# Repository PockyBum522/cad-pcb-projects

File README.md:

# cad-pcb-projects
Various PCB projects, mostly in KiCAD

## WT32-ETH01 Programming Shield

## ESP32-DevKitC-1 Prototype Shield

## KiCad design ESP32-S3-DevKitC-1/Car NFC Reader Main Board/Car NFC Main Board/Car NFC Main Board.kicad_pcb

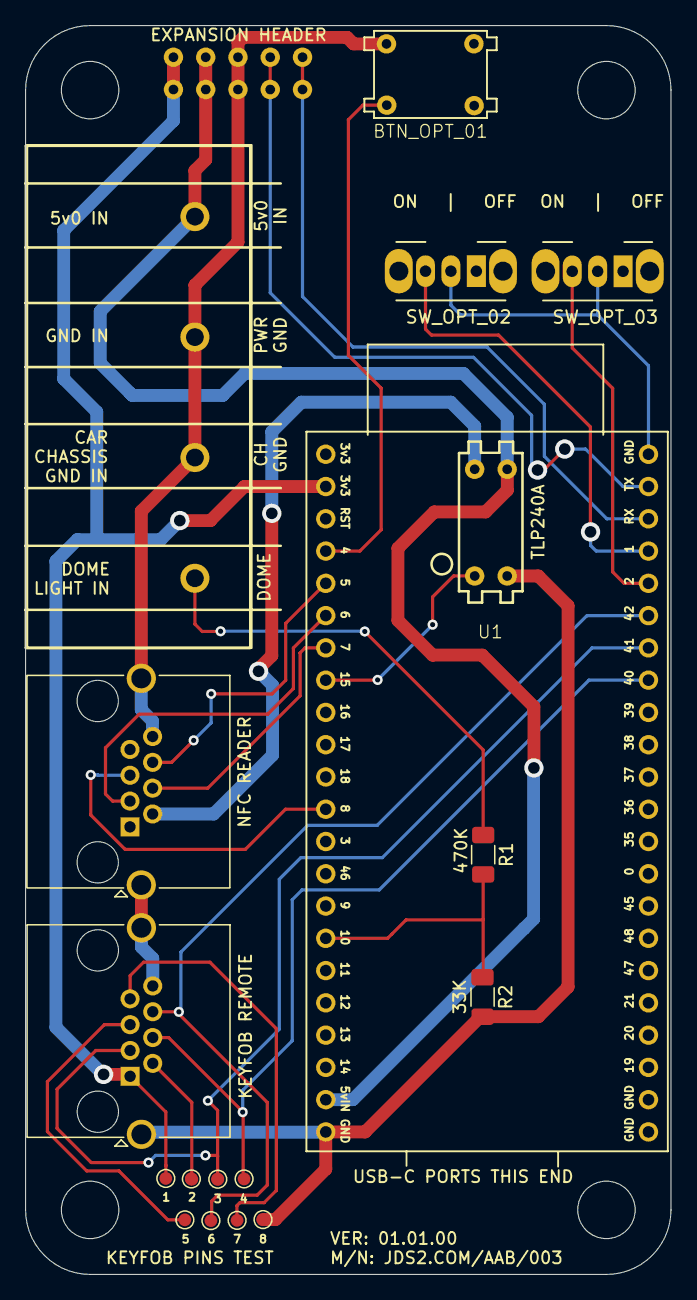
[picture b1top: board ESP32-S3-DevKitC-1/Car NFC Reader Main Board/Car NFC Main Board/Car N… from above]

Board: 2 copper layers, 50.8 x 98.3 mm, 11 parts (0 on the bottom side), 19 nets.

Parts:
BTN_OPT_01: SW_Push_Momentary; MOMENTARY_BUTTON
J1: YK441 Screw Terminal Block_CAR_NFC
J2, J3: AMPHENOL_RJHSE-5380-ND; RJ45_Amphenol_RJHSE5380
J4: 10_PIN_HEADER; 8_PIN_HEADER
R1, R2: R; R_1206_3216Metric_Pad1.30x1.75mm_HandSolder
SW_OPT_02, SW_OPT_03: SW_SPDT; SW_CuK_OS102011MA1QN1_SPDT_Angled
U1: TLP240A
U2: ESP32-S3-DevKitC-1_DAVID; ESP32-S3-DEVKITC_DAVID

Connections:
+3.3V: J2.1 (1/WHT-ORANGE), J4.3 (3V3), U2.52 (3V3)
+5V: J1.1, J4.2 (5V), U1.4 (C), U2.51 (5v0_IN)
/DOME: J1.4, R1.1
GND: BTN_OPT_01.1, J1.2, J1.3, J2.8 (8/BROWN), J2.SH (SHIELD), J3.7 (7/WHT-BROWN), J3.SH (SHIELD), J4.1 (GND), R2.2, SW_OPT_02.2 (B), SW_OPT_03.2 (B), U1.6 (K), U2.50 (GND)
unnamed: J2.3 (3/WHT-GREEN), U2.41 (GPIO41_MTMS/CLK_OUT1)
unnamed: J2.4 (4/BLUE), U2.40 (GPIO40_MTDO/CLK_OUT2)
unnamed: J2.6 (6/GREEN), U2.42 (GPIO42_MTMS)
unnamed: J3.2 (2/ORANGE), U1.3 (E)
unnamed: J3.3 (3/WHT-GREEN), U2.6 (GPIO6_TOUCH6/ADC1_CH5/RTC)
unnamed: J3.4 (4/BLUE), U2.7 (GPIO7_TOUCH7/ADC1_CH6/RTC)
unnamed: J3.5 (5/WHT-BLUE), U2.8 (GPIO8_TOUCH8/ADC1_CH7/RTC)
unnamed: J3.6 (6/GREEN), U2.5 (GPIO5_TOUCH5/ADC1_CH4/RTC)
unnamed: J4.5 (RX0), U2.44 (GPIO44_U0RXD/CLK_OUT2)
unnamed: J4.4 (TX0), U2.43 (GPIO43_U0TXD/CLK_OUT1)
unnamed: SW_OPT_02.3 (C), U2.1 (GPIO1_TOUCH1/ADC1_CH0/RTC)
unnamed: SW_OPT_03.3 (C), U2.2 (GPIO2_TOUCH2/ADC1_CH1/RTC)
unnamed: U1.1 (A), U2.15 (GPIO15_U0RTS/ADC2_CH4/XTAL_32K_P/RTC)
unnamed: BTN_OPT_01.2, U2.4 (GPIO4_TOUCH4/ADC1_CH3/RTC)
unnamed: R1.2, R2.1, U2.10 (GPIO10_TOUCH10/ADC1_CH9/FSPICS0/SUBSPIC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)

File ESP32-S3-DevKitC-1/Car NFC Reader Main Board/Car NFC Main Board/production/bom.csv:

Designator,Footprint,Quantity,Value,LCSC Part #
BTN_OPT_01,MOMENTARY_BUTTON,1,SW_Push_Momentary,
J1,YK441 Screw Terminal Block_CAR_NFC,1,~,
"J2, J3",RJ45_Amphenol_RJHSE5380,2,AMPHENOL_RJHSE-5380-ND,
J4,8_PIN_HEADER,1,10_PIN_HEADER,
"R1, R2",1206,2,R,
"SW_OPT_02, SW_OPT_03",SW_CuK_OS102011MA1QN1_SPDT_Angled,2,SW_SPDT,
U1,TLP240A,1,TLP240A,
U2,ESP32-S3-DEVKITC_DAVID,1,ESP32-S3-DevKitC-1_DAVID,

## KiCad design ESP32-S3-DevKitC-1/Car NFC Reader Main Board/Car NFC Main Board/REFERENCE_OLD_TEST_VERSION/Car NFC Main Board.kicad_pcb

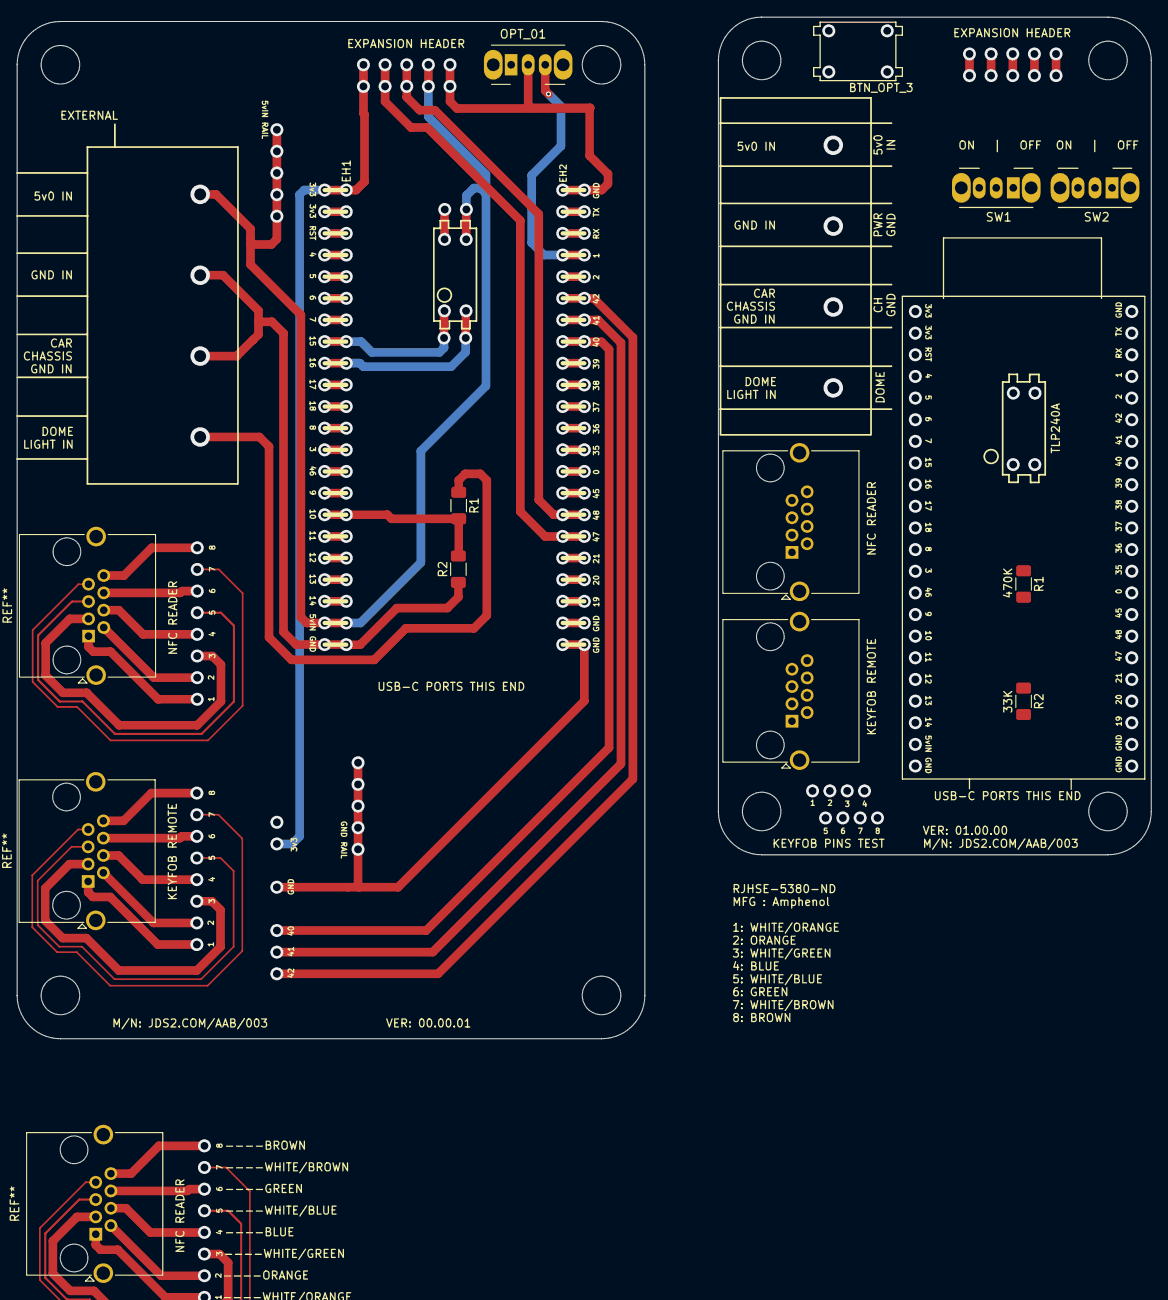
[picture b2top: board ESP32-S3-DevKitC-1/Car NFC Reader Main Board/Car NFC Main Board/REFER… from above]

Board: 2 copper layers, 133.1 x 119.9 mm, 7 parts (0 on the bottom side), 3 nets.

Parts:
OPT_01: SW_Slide_SPDT_Angled_CK_OS102011MA1Q
R1, R1#2: 470K; R_1206_3216Metric_Pad1.30x1.75mm_HandSolder
R2: 33K; R_1206_3216Metric_Pad1.30x1.75mm_HandSolder
R2#2: 200R; R_1206_3216Metric_Pad1.30x1.75mm_HandSolder
SW1, SW2: SW_SPDT; SW_CuK_OS102011MA1QN1_SPDT_Angled

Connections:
GND: OPT_01.2, R2.2, R2#2.1, SW1.2 (B), SW2.2 (B)
unnamed: R1.2, R2.1
POST_DIVIDER_DOME: R1#2.2, R2#2.2

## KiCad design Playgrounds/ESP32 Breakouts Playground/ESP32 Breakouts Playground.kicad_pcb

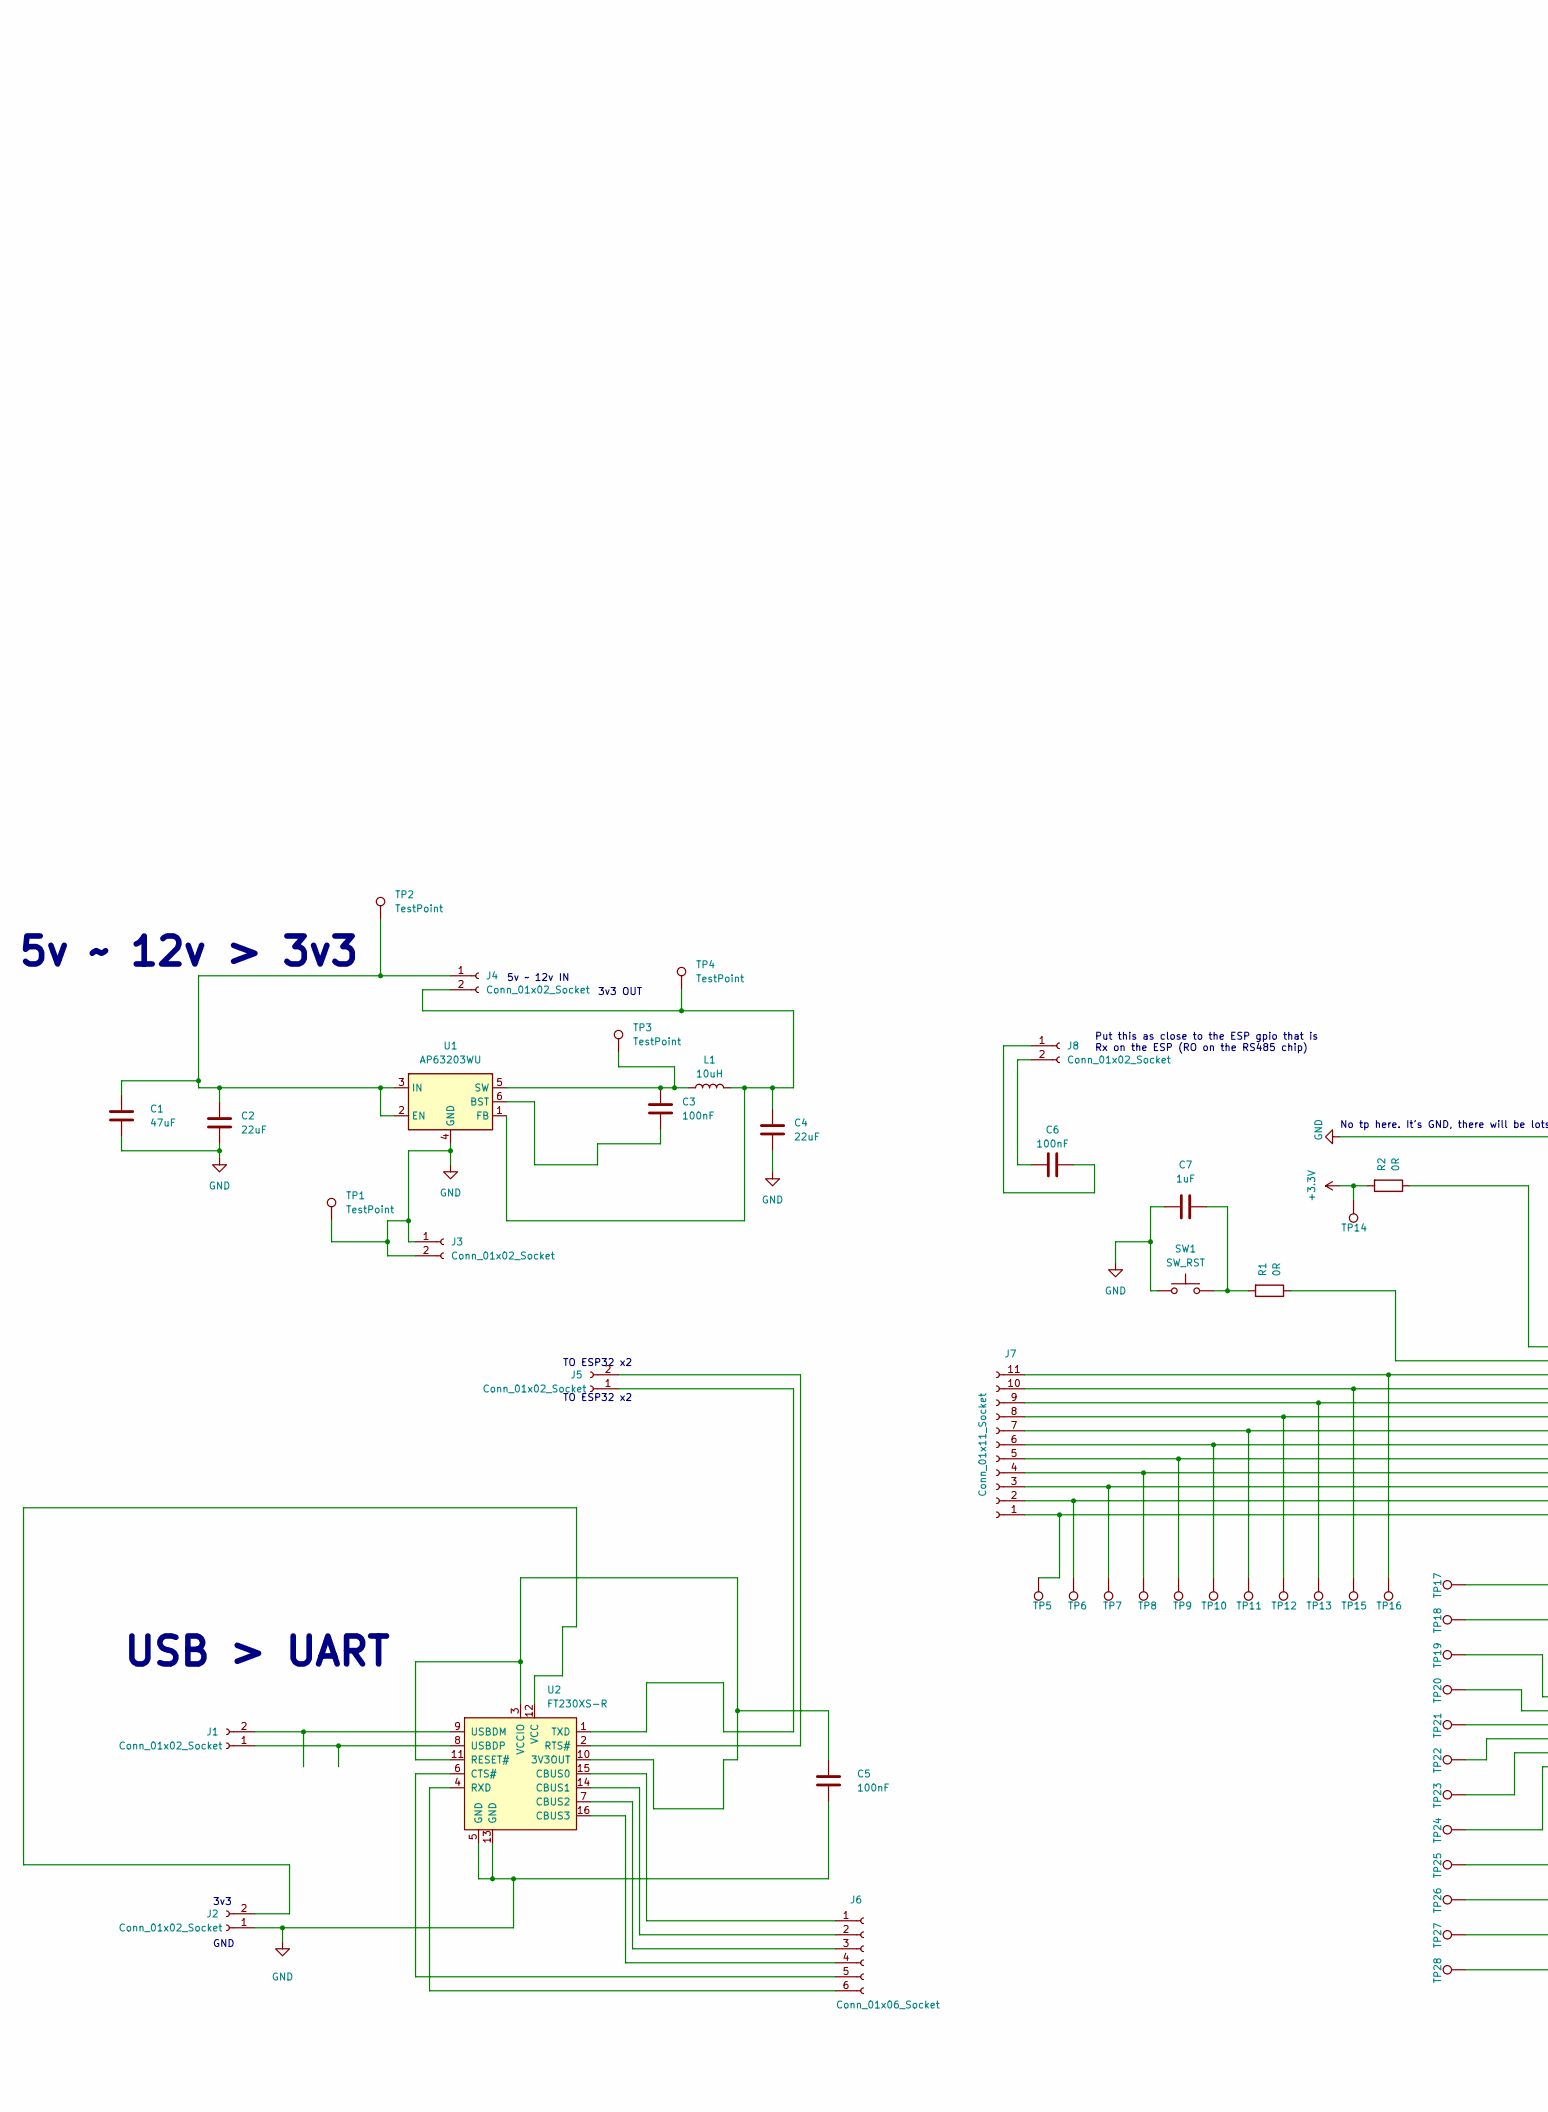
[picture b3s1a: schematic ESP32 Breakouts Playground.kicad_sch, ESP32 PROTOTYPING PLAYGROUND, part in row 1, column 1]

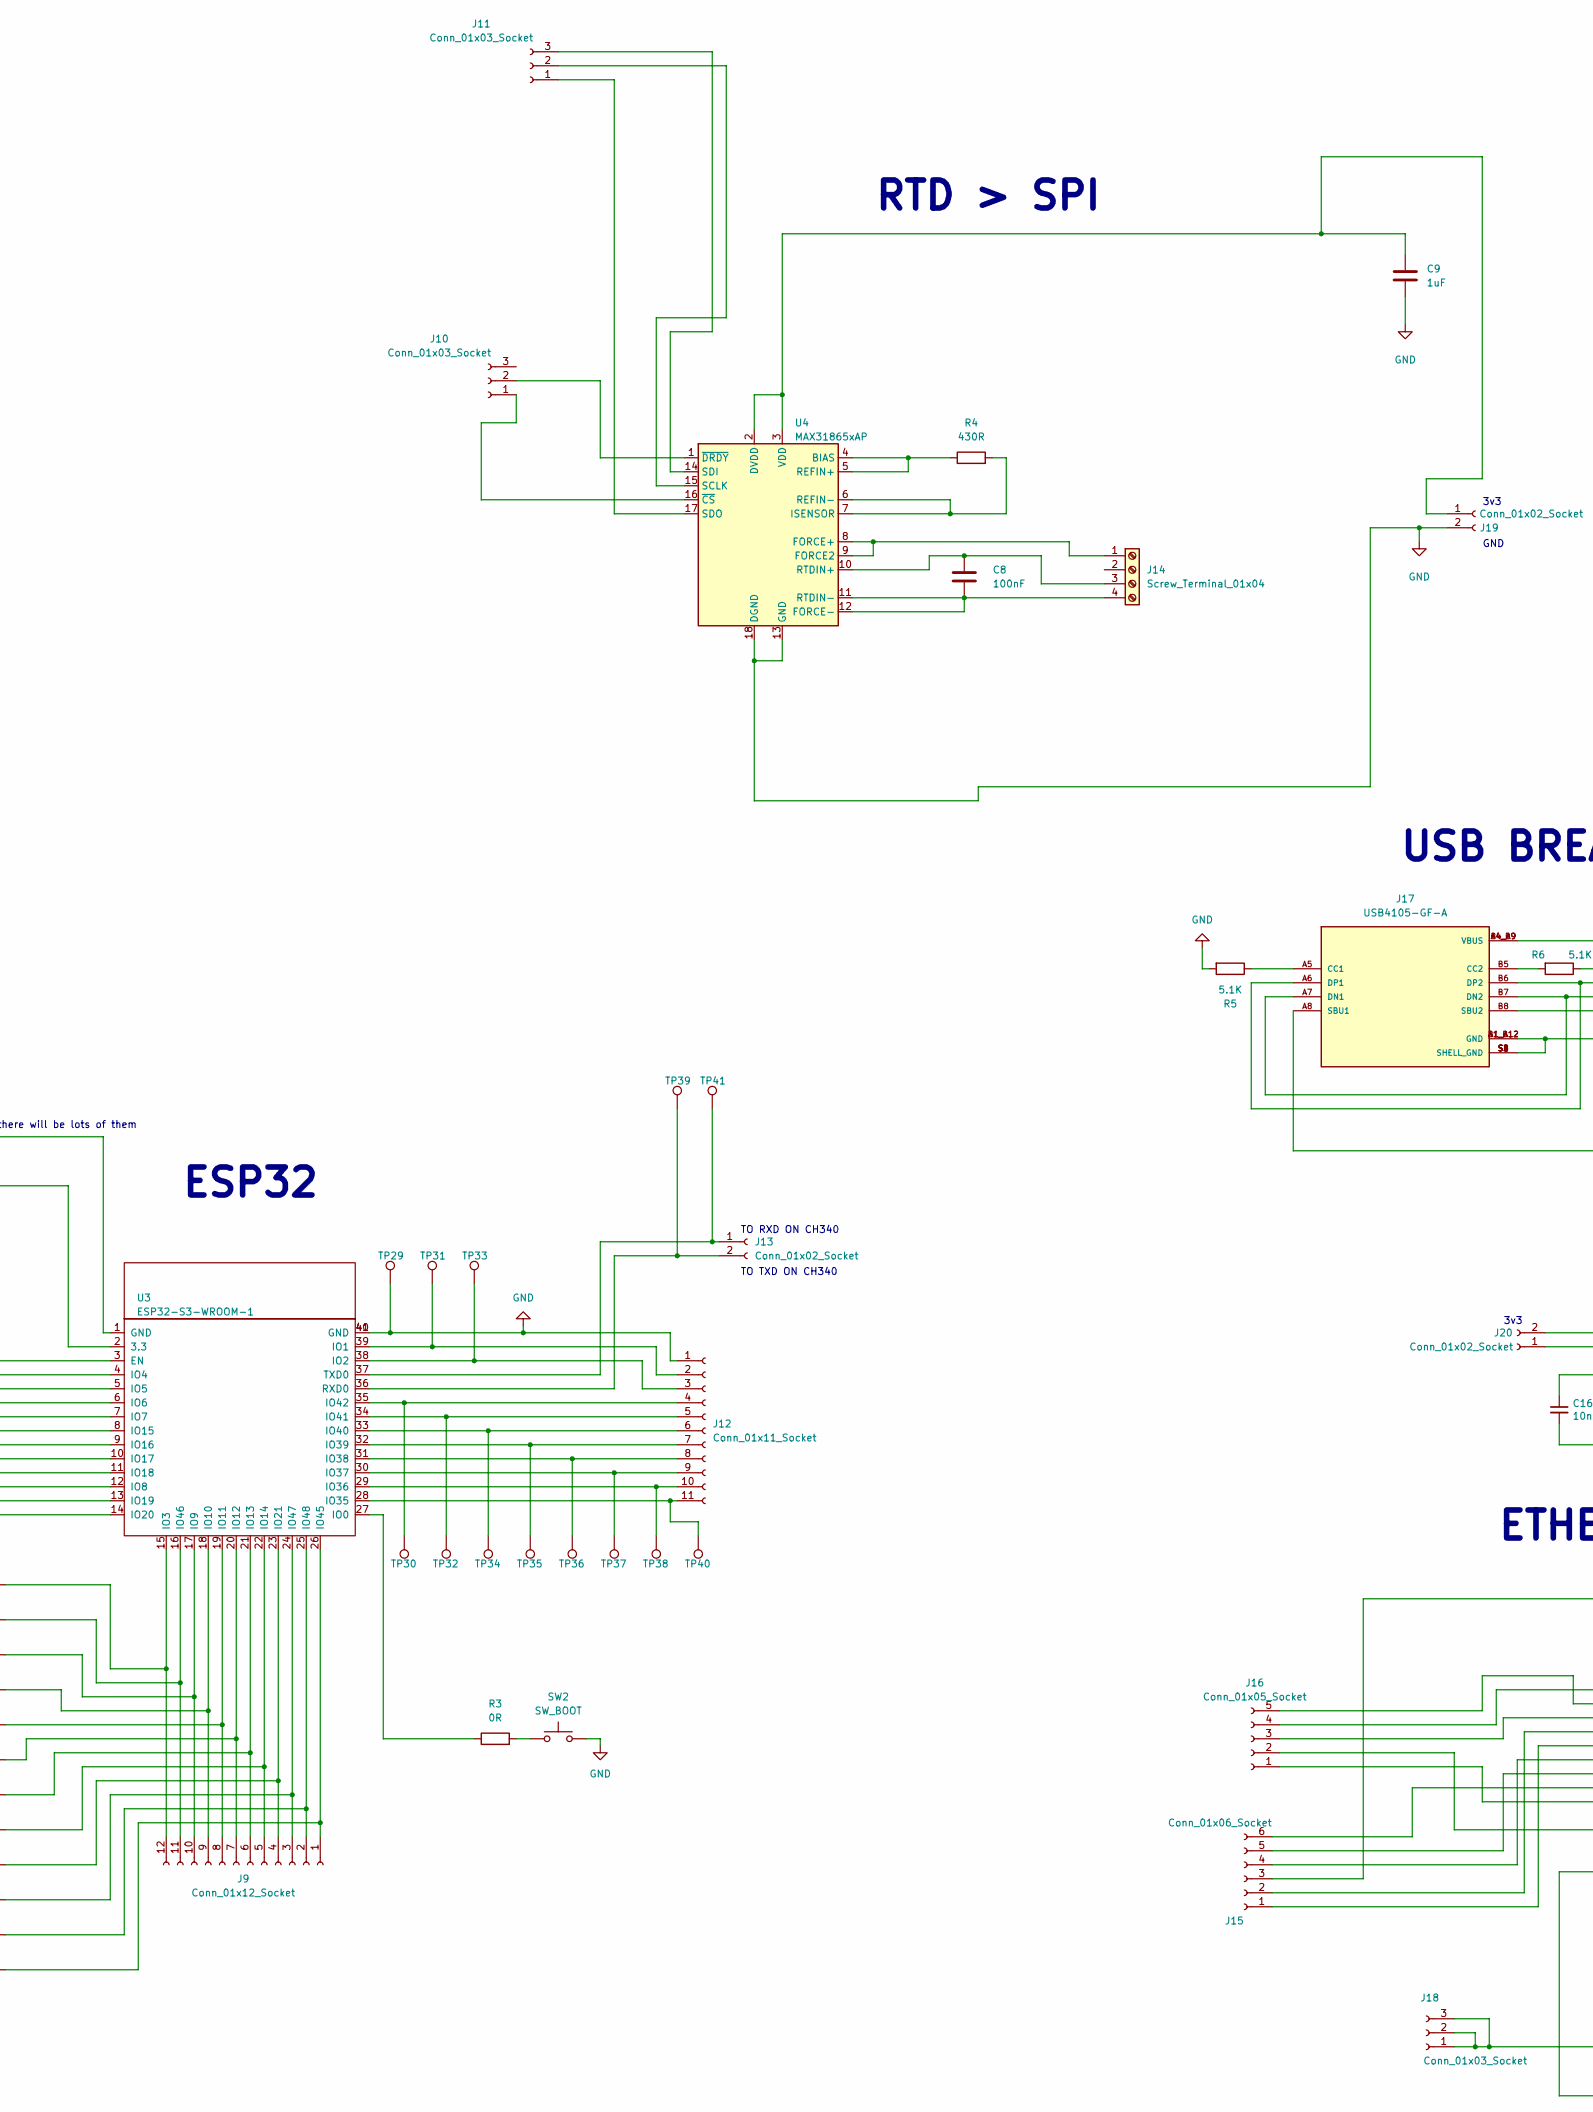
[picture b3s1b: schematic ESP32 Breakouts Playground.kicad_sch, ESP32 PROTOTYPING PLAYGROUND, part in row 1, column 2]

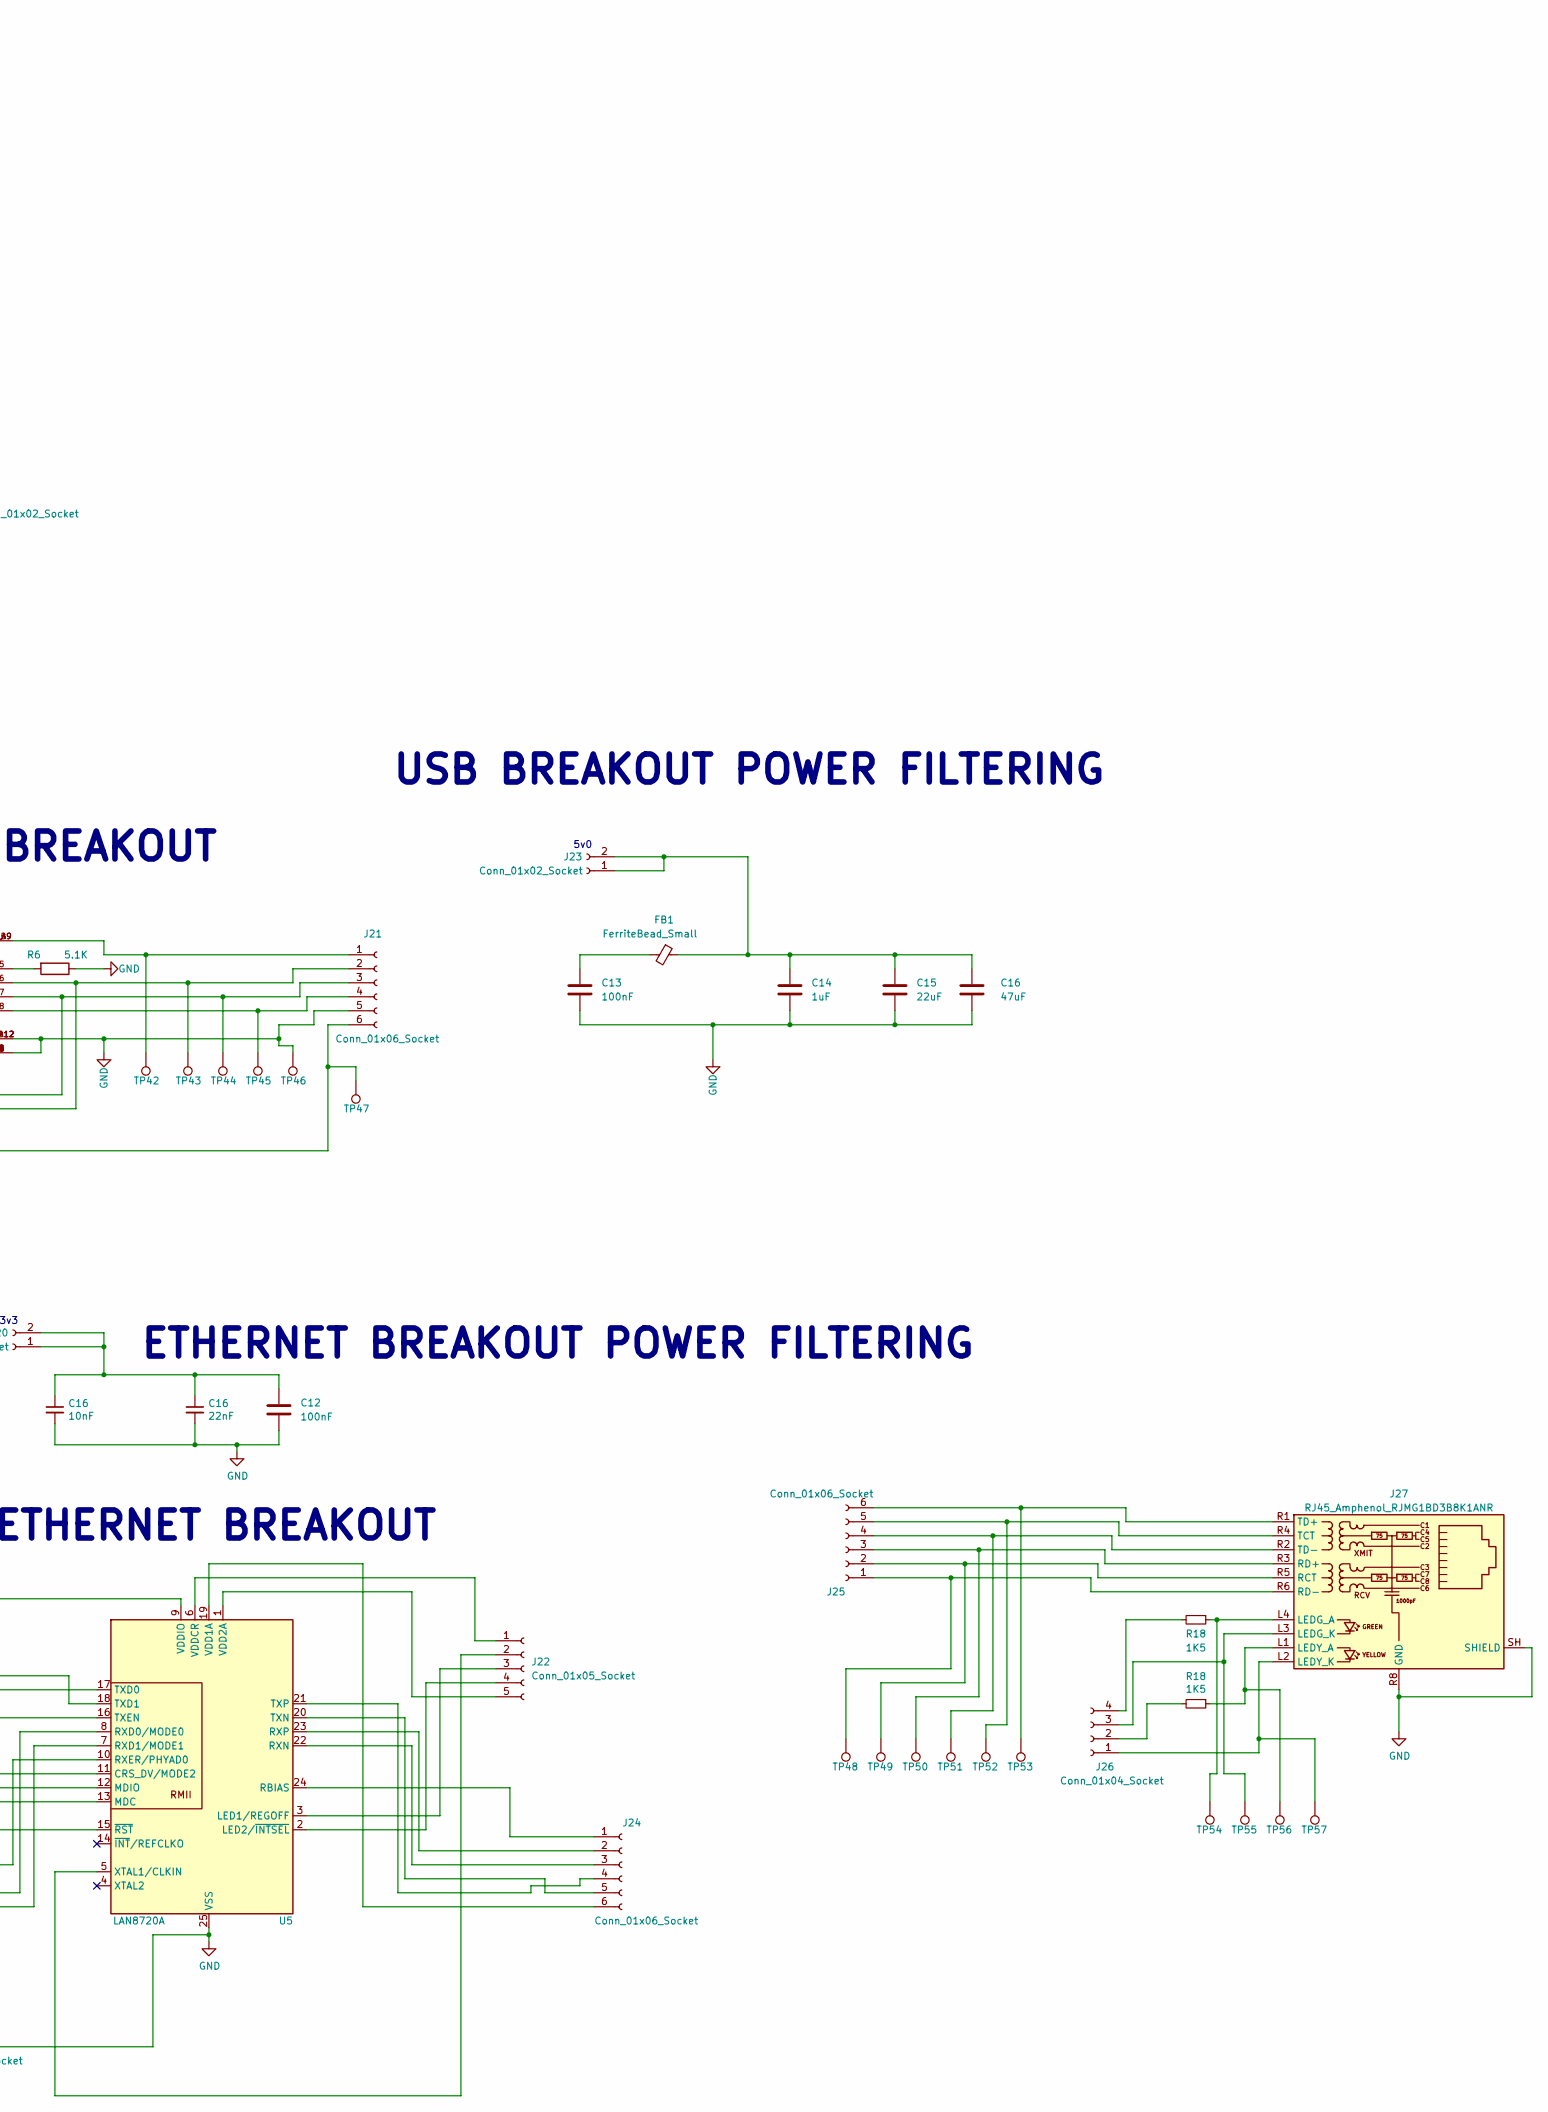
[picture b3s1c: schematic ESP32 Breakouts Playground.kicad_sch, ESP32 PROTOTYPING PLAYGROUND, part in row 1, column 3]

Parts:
C1: 47uF; CP_Elec_5x5.3
C2, C4, C15: 22uF; C_1206_3216Metric
C3, C5, C6, C8, C12, C13: 100nF; C_1206_3216Metric
C7, C9, C14: 1uF; C_1206_3216Metric
C16: 10nF; C_1206_3216Metric
FB1: FerriteBead_Small; L_0603_1608Metric
J1, J2, J3, J4, J5, J8, J13, J19, J20, J23: Conn_01x02_Socket; PinHeader_1x02_P2.54mm_Vertical
J6, J15, J21, J24, J25: Conn_01x06_Socket; PinHeader_1x06_P2.54mm_Vertical
J7, J12: Conn_01x11_Socket; PinHeader_1x11_P2.54mm_Vertical
J9: Conn_01x12_Socket; PinHeader_1x12_P2.54mm_Vertical
J10, J11, J18: Conn_01x03_Socket; PinHeader_1x03_P2.54mm_Vertical
J14: Screw_Terminal_01x04; TerminalBlock_RND_205-00069_1x04_P7.50mm_Horizontal
J16, J22: Conn_01x05_Socket; PinHeader_1x05_P2.54mm_Vertical
J17: USB4105-GF-A; GCT_USB4105-GF-A; PARTREV A3
J26: Conn_01x04_Socket; PinHeader_1x04_P2.54mm_Vertical
J27: RJ45_Amphenol_RJMG1BD3B8K1ANR
L1: 10uH; L_Taiyo-Yuden_NR-60xx
R1, R2, R3: 0R; R_2010_5025Metric_Pad1.40x2.65mm_HandSolder
R4: 430R; R_0603_1608Metric
R5, R6: 5.1K; R_0603_1608Metric
R18: 1K5; R_0603_1608Metric
SW1: SW_RST; SW_SPST_EVPBF
SW2: SW_BOOT; SW_SPST_EVPBF
TP1, TP2, TP3, TP4, TP5, TP6, TP7, TP8, TP9, TP10, TP11, TP12, TP13, TP14, TP15, TP16, TP17, TP18, TP19, TP20, TP21, TP22, TP23, TP24, TP25, TP26, TP27, TP28, TP29, TP30, TP31, TP32, TP33, TP34, TP35, TP36, TP37, TP38, TP39, TP40, TP41, TP42, TP43, TP44, TP45, TP46, TP47, TP48, TP49, TP50, TP51, TP52, TP53, TP54, TP55, TP56, TP57: TestPoint; KOA_RCWCTE_TEST_POINT
U1: AP63203WU; TSOT-23-6
U2: FT230XS-R; SOIC-16_W3.90mm; MPN FT230XS-R; Digi-Key_PN 768-1135-1-ND
U3: ESP32-S3-WROOM-1; ESP32-S3-wrooom
U4: MAX31865xAP; SSOP-20_5.3x7.2mm_P0.65mm
U5: LAN8720A; VQFN-24-1EP_4x4mm_P0.5mm_EP2.5x2.5mm_ThermalVias

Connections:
+3.3V: R2.2, TP14.1
GND: C1.2, C2.2, C4.2, C5.1, C7.1, C9.1, C12.2, C13.2, C14.2, C15.2, C16.2, J2.1, J3.1, J3.2, J12.1, J17.A1_B12 (GND), J17.B1_A12 (GND), J17.S1 (SHELL_GND), J17.S2 (SHELL_GND), J17.S3 (SHELL_GND), J17.S4 (SHELL_GND), J18.1, J18.2, J18.3, J19.2, J21.5, J27.R8 (GND), J27.SH (SHIELD), R5.2, R6.1, SW1.1, SW2.2, TP1.1, TP29.1, TP46.1, U1.4 (GND), U2.5 (GND), U2.13 (GND), U3.1 (GND), U3.40 (GND), U3.41 (GND), U4.13 (GND), U4.18 (DGND), U4.19 (GND), U5.25 (VSS); also elsewhere on the board
unnamed: C7.2, R1.2, SW1.2
unnamed: C13.1, FB1.2
unnamed: J1.1, U2.8 (USBDP)
unnamed: J1.2, U2.9 (USBDM)
unnamed: J2.2, U2.12 (VCC)
unnamed: C1.1, C2.1, J4.1, TP2.1, U1.2 (EN), U1.3 (IN)
unnamed: C4.1, J4.2, L1.2, TP4.1, U1.1 (FB)
unnamed: J5.1, U2.1 (TXD)
unnamed: J5.2, U2.2 (RTS#)
unnamed: J6.1, U2.15 (CBUS0)
unnamed: J6.2, U2.14 (CBUS1)
unnamed: J6.3, U2.7 (CBUS2)
unnamed: J6.4, U2.16 (CBUS3)
unnamed: J6.5, U2.6 (CTS#)
unnamed: J6.6, U2.4 (RXD)
unnamed: J7.1, TP5.1, U3.14 (IO20)
unnamed: J7.2, TP6.1, U3.13 (IO19)
unnamed: J7.3, TP7.1, U3.12 (IO8)
unnamed: J7.4, TP8.1, U3.11 (IO18)
unnamed: J7.5, TP9.1, U3.10 (IO17)
unnamed: J7.6, TP10.1, U3.9 (IO16)
unnamed: J7.7, TP11.1, U3.8 (IO15)
unnamed: J7.8, TP12.1, U3.7 (IO7)
unnamed: J7.9, TP13.1, U3.6 (IO6)
unnamed: J7.10, TP15.1, U3.5 (IO5)
unnamed: J7.11, TP16.1, U3.4 (IO4)
unnamed: C6.2, J8.1
unnamed: C6.1, J8.2
unnamed: J9.1, TP28.1, U3.26 (IO45)
unnamed: J9.2, TP27.1, U3.25 (IO48)
unnamed: J9.3, TP26.1, U3.24 (IO47)
unnamed: J9.4, TP25.1, U3.23 (IO21)
unnamed: J9.5, TP24.1, U3.22 (IO14)
unnamed: J9.6, TP23.1, U3.21 (IO13)
unnamed: J9.7, TP22.1, U3.20 (IO12)
unnamed: J9.8, TP21.1, U3.19 (IO11)
unnamed: J9.9, TP20.1, U3.18 (IO10)
unnamed: J9.10, TP19.1, U3.17 (IO9)
unnamed: J9.11, TP18.1, U3.16 (IO46)
unnamed: J9.12, TP17.1, U3.15 (IO3)
unnamed: J10.1, U4.16 (~CS)
unnamed: J10.2, U4.1 (~DRDY)
unnamed: J11.1, U4.17 (SDO)
unnamed: J11.2, U4.15 (SCLK)
unnamed: J11.3, U4.14 (SDI)
unnamed: J12.2, TP31.1, U3.39 (IO1)
unnamed: J12.3, TP33.1, U3.38 (IO2)
unnamed: J12.4, TP30.1, U3.35 (IO42)
unnamed: J12.5, TP32.1, U3.34 (IO41)
unnamed: J12.6, TP34.1, U3.33 (IO40)
unnamed: J12.7, TP35.1, U3.32 (IO39)
unnamed: J12.8, TP36.1, U3.31 (IO38)
unnamed: J12.9, TP37.1, U3.30 (IO37)
unnamed: J12.10, TP38.1, U3.29 (IO36)
unnamed: J12.11, TP40.1, U3.28 (IO35)
unnamed: J13.1, TP41.1, U3.37 (TXD0)
unnamed: J13.2, TP39.1, U3.36 (RXD0)
unnamed: J14.1, U4.8 (FORCE+), U4.9 (FORCE2)
unnamed: C8.2, J14.3, U4.10 (RTDIN+)
unnamed: C8.1, J14.4, U4.11 (RTDIN-), U4.12 (FORCE-)
unnamed: J15.1, U5.7 (RXD1/MODE1)
unnamed: J15.2, U5.8 (RXD0/MODE0)
unnamed: J15.3, U5.9 (VDDIO)
unnamed: J15.4, U5.10 (RXER/PHYAD0)
unnamed: J15.5, U5.11 (CRS_DV/MODE2)
unnamed: J15.6, U5.12 (MDIO)
unnamed: J16.1, U5.13 (MDC)
unnamed: J16.2, U5.15 (~RST)
unnamed: J16.3, U5.16 (TXEN)
unnamed: J16.4, U5.17 (TXD0)
unnamed: J16.5, U5.18 (TXD1)
unnamed: J17.A5 (CC1), R5.1
unnamed: J17.B5 (CC2), R6.2
unnamed: J17.A7 (DN1), J17.B7 (DN2), J21.3, TP44.1
unnamed: J17.A6 (DP1), J17.B6 (DP2), J21.2, TP43.1
unnamed: J17.A8 (SBU1), J21.6, TP47.1
unnamed: J17.B8 (SBU2), J21.4, TP45.1
unnamed: C9.2, J19.1, U4.2 (DVDD), U4.3 (VDD)
unnamed: J17.A4_B9 (VBUS), J17.B4_A9 (VBUS), J21.1, TP42.1
unnamed: J22.1, U5.6 (VDDCR)
unnamed: J22.2, U5.5 (XTAL1/CLKIN)
unnamed: J22.3, U5.3 (LED1/REGOFF)
unnamed: J22.4, U5.2 (LED2/~INTSEL)
unnamed: J22.5, U5.1 (VDD2A)
unnamed: J24.1, U5.24 (RBIAS)
unnamed: J24.2, U5.23 (RXP)
unnamed: J24.3, U5.22 (RXN)
unnamed: J24.4, U5.21 (TXP)
unnamed: J24.5, U5.20 (TXN)
unnamed: J24.6, U5.19 (VDD1A)
unnamed: J25.1, J27.R6 (RD-), TP48.1
unnamed: J25.2, J27.R5 (RCT), TP49.1
unnamed: J25.3, J27.R3 (RD+), TP50.1
unnamed: J25.4, J27.R2 (TD-), TP51.1
unnamed: J25.5, J27.R4 (TCT), TP52.1
unnamed: J25.6, J27.R1 (TD+), TP53.1
unnamed: J26.1, J27.L2 (LEDY_K), TP57.1
unnamed 99: J26.2; also elsewhere on the board
unnamed: J26.3, J27.L3 (LEDG_K), TP55.1
unnamed 101: J26.4; also elsewhere on the board
unnamed 102: J27.L4 (LEDG_A), TP54.1; also elsewhere on the board
unnamed 103: J27.L1 (LEDY_A), TP56.1; also elsewhere on the board
unnamed: R3.2, SW2.1
unnamed: C3.2, U1.6 (BST)
unnamed: C3.1, L1.1, TP3.1, U1.5 (SW)
unnamed: C5.2, U2.3 (VCCIO), U2.10 (3V3OUT), U2.11 (RESET#)
unnamed: R2.1, U3.2 (3.3)
unnamed: R1.1, U3.3 (EN)
unnamed: R3.1, U3.27 (IO0)
unnamed: R4.1, U4.4 (BIAS), U4.5 (REFIN+)
unnamed: R4.2, U4.6 (REFIN-), U4.7 (ISENSOR)

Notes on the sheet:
GND
ETHERNET BREAKOUT
ETHERNET BREAKOUT POWER FILTERING
5v0
3v3
USB BREAKOUT POWER FILTERING
USB > UART
3v3 OUT
RTD > SPI
TO RXD ON CH340
3v3
No tp here. It's GND, there will be lots of them
Put this as close to the ESP gpio that is Rx on the ESP (RO on the RS485 chip)
5v ~ 12v > 3v3
TO TXD ON CH340
5v ~ 12v IN
TO ESP32 x2
USB BREAKOUT
ESP32

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
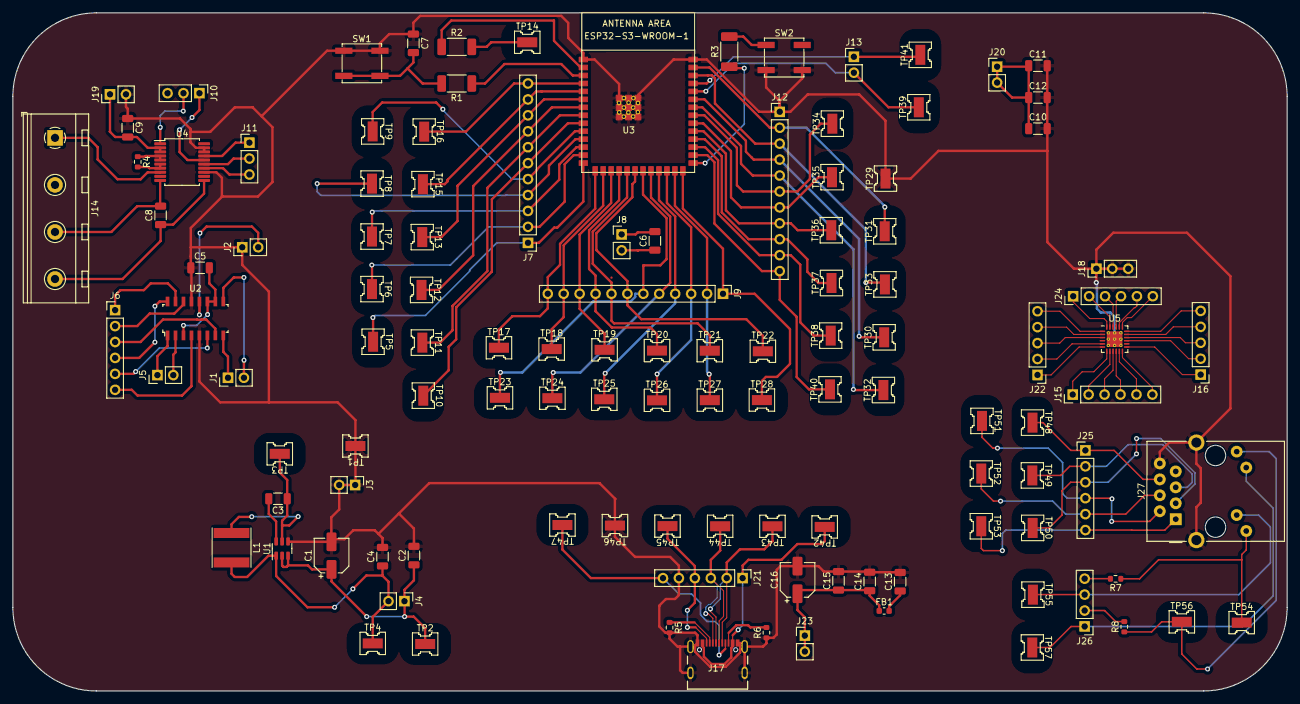
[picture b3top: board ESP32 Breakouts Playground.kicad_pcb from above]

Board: 2 copper layers, 203.1 x 108.1 mm, 117 parts (0 on the bottom side), 115 nets.

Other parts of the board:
C10: 10nF; C_1206_3216Metric
C11: 22nF; C_1206_3216Metric
R7, R8: 1K5; R_0603_1608Metric

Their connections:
GND: C10.2, C11.2; also elsewhere on the board
unnamed 99: R8.2; also elsewhere on the board
unnamed 101: R7.2; also elsewhere on the board
unnamed 102: R7.1; also elsewhere on the board
unnamed 103: R8.1; also elsewhere on the board

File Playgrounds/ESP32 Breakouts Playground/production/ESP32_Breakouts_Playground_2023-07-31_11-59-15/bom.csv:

Designator,Footprint,Quantity,Value,LCSC Part #
"C1, C16",CP_Elec_5x5.3,2,47uF,
C11,1206,1,22nF,
"C12, C13, C3, C5, C6, C8",1206,6,100nF,
"C14, C7, C9",1206,3,1uF,
"C15, C2, C4",1206,3,22uF,
FB1,0603,1,FerriteBead_Small,
"J1, J13, J19, J2, J20, J23, J3, J4, J5, J8",PinHeader_1x02_P2.54mm_Vertical,10,Conn_01x02_Socket,
"J10, J11, J18",PinHeader_1x03_P2.54mm_Vertical,3,Conn_01x03_Socket,
"J12, J7",PinHeader_1x11_P2.54mm_Vertical,2,Conn_01x11_Socket,
J14,TerminalBlock_RND_205-00069_1x04_P7.50mm_Horizontal,1,Screw_Terminal_01x04,
"J15, J21, J24, J25, J6",PinHeader_1x06_P2.54mm_Vertical,5,Conn_01x06_Socket,
"J16, J22",PinHeader_1x05_P2.54mm_Vertical,2,Conn_01x05_Socket,
J17,GCT_USB4105-GF-A,1,USB4105-GF-A,
J26,PinHeader_1x04_P2.54mm_Vertical,1,Conn_01x04_Socket,
J27,RJ45_Amphenol_RJMG1BD3B8K1ANR,1,RJ45_Amphenol_RJMG1BD3B8K1ANR,
J9,PinHeader_1x12_P2.54mm_Vertical,1,Conn_01x12_Socket,
L1,L_Taiyo-Yuden_NR-60xx,1,10uH,
"R1, R2, R3",2010,3,0R,
R4,0603,1,430R,
"R5, R6",0603,2,5.1K,
"R7, R8",0603,2,1K5,
SW1,SW_SPST_EVPBF,1,SW_RST,
SW2,SW_SPST_EVPBF,1,SW_BOOT,
"TP1, TP10, TP11, TP12, TP13, TP14, TP15, TP16, TP17, TP18, TP19, TP2, TP20, TP21, TP22, TP23, TP24, TP25, TP26, TP27, TP28, TP29, TP3, TP30, TP31, TP32, TP33, TP34, TP35, TP36, TP37, TP38, TP39, TP4, TP40, TP41, TP42, TP43, TP44, TP45, TP46, TP47, TP48, TP49, TP5, TP50, TP51, TP52, TP53, TP54, TP55, TP56, TP57, TP6, TP7, TP8, TP9",KOA_RCWCTE_TEST_POINT,57,TestPoint,
U1,TSOT-23-6,1,AP63203WU,
U2,SOIC-16_W3.90mm,1,FT230XS-R,FT230XS-R
U3,ESP32-S3-wrooom,1,ESP32-S3-WROOM-1,
U4,SSOP-20_5.3x7.2mm_P0.65mm,1,MAX31865xAP,
U5,VQFN-24-1EP_4x4mm_P0.5mm_EP2.5x2.5mm_ThermalVias,1,LAN8720A,

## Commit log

2023-05-27 Added ESP32-S3-DevKitC-1 Proto shield EasyEDA files
2023-05-27 Fixed pin numbering on pads
2023-05-27 Removed pads blocking silkscreen after array
2023-05-27 Fixed text not on silkscreen layer
    - Added dual silkscreen layer board file
2023-05-27 Adding WT32-ETH01 Programming board
2023-06-28 Migrating to EasyEDA standard
2023-06-28 Named things properly, added double sided project
2023-07-05 Added header ref width to ETH01
2023-07-05 Update Version History.md
    VER: 00.00.03
    * Added trace screenprinting to top layer since traces themselves aren't super obvious
    * Widened space between headers as I mismeasured the ESP32 dev board
    * Due to the above line, added a middle column of pads with no traces to anywhere
    * Updated rev screenprint number
    * Added header H16 since board was widened
2023-07-05 Updated actual project files for REV 00.00.03
2023-07-05 Added regions around GPIO coupled pads
2023-07-05 Fixed regions around GPIO ids
2023-07-21 Moved ESP32-S3 proto board project to Kicad
2023-07-21 Reorganizing files to parent folder so no duplication
2023-07-22 Finished front side of ESP32-S3 proto shield in kicad
2023-07-22 version 01.00.00 as ordered through JLCPCB
    - Rails moved back
    - Two switch/buttons added
    - Started using KICad
2023-07-22 Moved WT32-ETH01 programming board to kicad template
    Not completed at all, just getting started by copying ESP32 proto board
2023-07-22 I lied this is v1.0
2023-07-28 Adding ESP32 breakout board
2023-07-31 Finished routing
2023-07-31 ordered today jlcpcb
2023-09-12 Removed old project for one-sided board
2024-03-02 V00.02.00 of WT32-ETH01 programming/proto board ordered
2024-06-11 Added robot arm boards WIP
2024-06-11 Added car NFC mainboard WIP
2024-06-11 Adding car nfc board WIP
2024-06-13 Car NFC proto board as ordered on 2024-06-13
2024-06-14 Fixed tented vias issue
2024-06-25 Final submitted version
2024-06-25 Update fp-info-cache
2024-06-26 I honestly have no idea
2024-07-02 Added ethernet port pinout notes
2024-07-15 Gave new resistor values matching what's tested in the honda
2024-07-16 NFC reader board version submitted to JLCPCB
2024-07-22 Fixed PCB and schematic where GND pin on NFC reader ethernet port went to pin 7 instead of pin 8 like it should have
2024-07-23 Added case models and STL for car NFC board
2024-07-23 Moving things to right folders
2024-07-23 Updated case to have drain hole so wouldn't suction while printing
2024-08-08 Fix buttons, ver number, spacing, labels
    - Space header labels slightly further from center so can be seen when headers installed
    - Update version number
    - A tiny tiny bit more spacing to the ETH jack on mounted board
    - Fix button through-hole size to slightly larger
    - Fix button spacing to wider + taller for normal bent legs
2024-08-08 Version as submitted to jlcpcb
2024-11-05 Add ESP32-S3-DevKitC-1 PCB images to readme
    Making images side by side in readme
    Testing resized images in readme
    add images for readme
    Add ESP32 board images
    Add better image to readme
2026-03-28 Update class notes prior to first class
